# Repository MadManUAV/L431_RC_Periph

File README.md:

# L431_RC_Periph

A small ArduPilot DroneCAN peripheral board built around the STM32L431, under the [MadManUAV](https://github.com/MadManUAV) org.

**Status:** work in progress — hardware design.

## What it is

An `AP_Periph` CAN node: an STM32L431 paired with a TCAN CAN transceiver that hangs off a flight controller's CAN bus and handles RC/servo peripheral duties, running ArduPilot's AP_Periph firmware.

## Repo layout

- KiCad project — schematic (`L431_RC_Periph.kicad_sch`, with `AP_Periph` and `TCAN` sheets) and board (`L431_RC_Periph.kicad_pcb`).
- Shared symbols and footprints come from the [`mad_lib`](https://github.com/Cimos/mad_lib) submodule — clone with `--recurse-submodules`.
- KiBot CI (`options.yaml`, `build-panel.yaml`) builds the PCB, renders images, diffs revisions, panelises, and cuts a release datapack via the workflows in `.github/workflows`.

## License

GPL-3.0 — see [LICENSE.md](LICENSE.md).

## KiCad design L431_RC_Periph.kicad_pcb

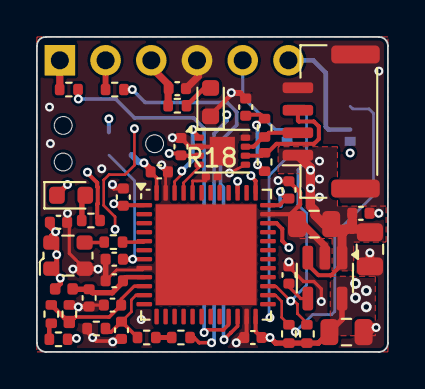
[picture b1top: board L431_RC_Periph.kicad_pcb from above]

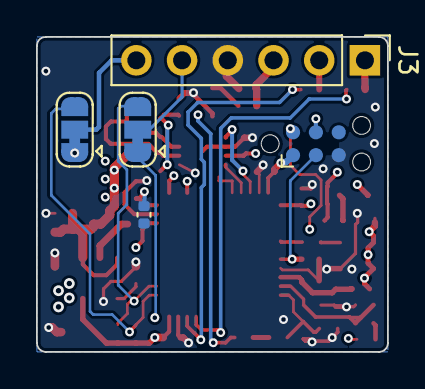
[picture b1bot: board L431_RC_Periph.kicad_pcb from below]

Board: 4 copper layers, 19.5 x 17.5 mm, 52 parts (5 on the bottom side), 33 nets.

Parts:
C1, C4, C6, C7, C8, C10, C15, C16, C17, C18, C19, C21, C25, C26, C27: 100nF; C_0402_1005Metric
C2, C3, C5: 10uF; C_0805_2012Metric
C12: 47nF; C_0402_1005Metric
D1: BLUE; LED_0603_1608Metric
D2: GREEN; LED_0603_1608Metric
FB1: BLM15PX330SN1D; L_0402_1005Metric
J1: CAN1; JST_GH_SM04B-GHS-TB_1x04-1MP_P1.25mm_Horizontal
J3: RC IF; PinHeader_1x06_P2.54mm_Vertical
J5: Conn_ARM_SWD_TagConnect_TC2030-NL; Tag-Connect_TC2030-IDC-NL_2x03_P1.27mm_Vertical
JP1, JP2: SolderJumper_3_Bridged12; SolderJumper-3_P1.3mm_Bridged12_RoundedPad1.0x1.5mm
R1, R2: 1K; R_0402_1005Metric
R3, R4, R5, R8, R9, R10, R15, R16: 5K1; R_0402_1005Metric
R6, R7, R13, R14, R17: 59R; R_0402_1005Metric
R18: 10K; R_0201_0603Metric
T1, T2, T3, T4: Tab
U1: PCB; BOM
U2: SPX3819M5-L-3-3; SOT-23-5
U3: TCAN1057; SON-8-1EP_3x2mm_P0.5mm_EP1.4x1.6mm
U4: STM32L431CCUx; QFN-48-1EP_7x7mm_P0.5mm_EP5.6x5.6mm
X1: ECS-2520MVLC-080-BP-TR; Oscillator_SMD_ECS_2520MV-xxx-xx-4Pin_2.5x2.0mm

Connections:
+3V3: C5.1, C10.1, C15.1, C16.1, C17.1, C18.1, C19.1, FB1.1, J5.1 (VCC), R15.1, R16.1, U2.5 (OUT), U3.5 (N/C), U4.1 (VBAT), U4.24 (VDD), U4.36 (VDD), U4.48 (VDD), X1.1 (Tri-State), X1.4 (VDD)
+5V: C1.2, C2.1, C3.1, C7.2, C27.1, J1.1, J3.3, R1.2, R2.2, U2.1 (IN), U2.3 (EN), U3.3 (VCC)
/AP_Periph/BOOT0: R18.1, U4.44 (PH3)
/AP_Periph/CAN1_RX: U3.4 (RXD), U4.45 (PB8)
/AP_Periph/CAN1_TX: U3.1 (TXD), U4.46 (PB9)
/AP_Periph/SWCLK: J5.4 (SWCLK), U4.37 (PA14)
/AP_Periph/SWDIO: J5.2 (SWDIO), U4.34 (PA13)
/AP_Periph/~RST: C21.1, J5.3 (~RESET), U4.7 (NRST)
/CAN1_H: J1.2, R13.2, U3.7 (CANH)
/CAN1_L: J1.3, R14.1, U3.6 (CANL)
/I2C2_SCL: JP2.3 (B), R16.2, U4.26 (PB13)
/I2C2_SDA: JP1.3 (B), R15.2, U4.27 (PB14)
/Out1: J3.5, JP1.2 (C)
/Out2: J3.6, JP2.2 (C)
/StatusLED: D2.1 (K), U4.39 (PB3)
/USART3_RX: R7.2, U4.22 (PB11)
/USART3_TX: R6.2, U4.21 (PB10)
/VBATT_C_MON: C6.2, R4.2, R5.1, U4.11 (PA1)
/VBATT_V_MON: C8.2, R9.2, R10.1, U4.10 (PA0)
GND: C1.1, C2.2, C3.2, C4.1, C5.2, C6.1, C7.1, C8.1, C10.2, C12.2, C15.2, C16.2, C17.2, C18.2, C19.2, C21.2, C25.2, C26.2, C27.2, D1.1 (K), J1.4, J1.MP (MountPin), J3.4, J5.5 (GND), R5.2, R10.2, R18.2, U2.2 (GND), U3.2 (GND), U3.8 (S), U3.9 (GND), U4.8 (VSSA), U4.23 (VSS), U4.35 (VSS), U4.47 (VSS), U4.49 (VSS), X1.2 (GND)
unnamed: C12.1, R13.1, R14.2
unnamed: D1.2 (A), R1.1
unnamed: D2.2 (A), R2.1
unnamed: J3.1, R6.1
unnamed: J3.2, R7.1
unnamed: JP1.1 (A), R8.1
unnamed: JP2.1 (A), R3.1
unnamed: R3.2, R4.1
unnamed: R8.2, R9.1
unnamed: C4.2, U2.4 (BP)
unnamed: R17.1, U4.5 (PH0)
unnamed: C25.1, C26.1, FB1.2, U4.9 (VDDA)
unnamed: R17.2, X1.3 (OUT)

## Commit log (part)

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2025-04-14 Add base project
2025-04-14 Add github workflow
2025-04-14 Add missing file
2025-04-14 Update workflow
2025-04-16 Finish routing and add option for using batt mon pads as I2C lines for added GPS
2025-04-16 Update name of github workflow
2025-04-16 Remove FID from BOM
2025-04-16 Add JLC PCB DRU file from Kibot Custom DRU git repo
2025-04-16 Update workflow to use panel file not pcb file
2025-04-22 Update to 6 pin headers and remove the two solder pads
